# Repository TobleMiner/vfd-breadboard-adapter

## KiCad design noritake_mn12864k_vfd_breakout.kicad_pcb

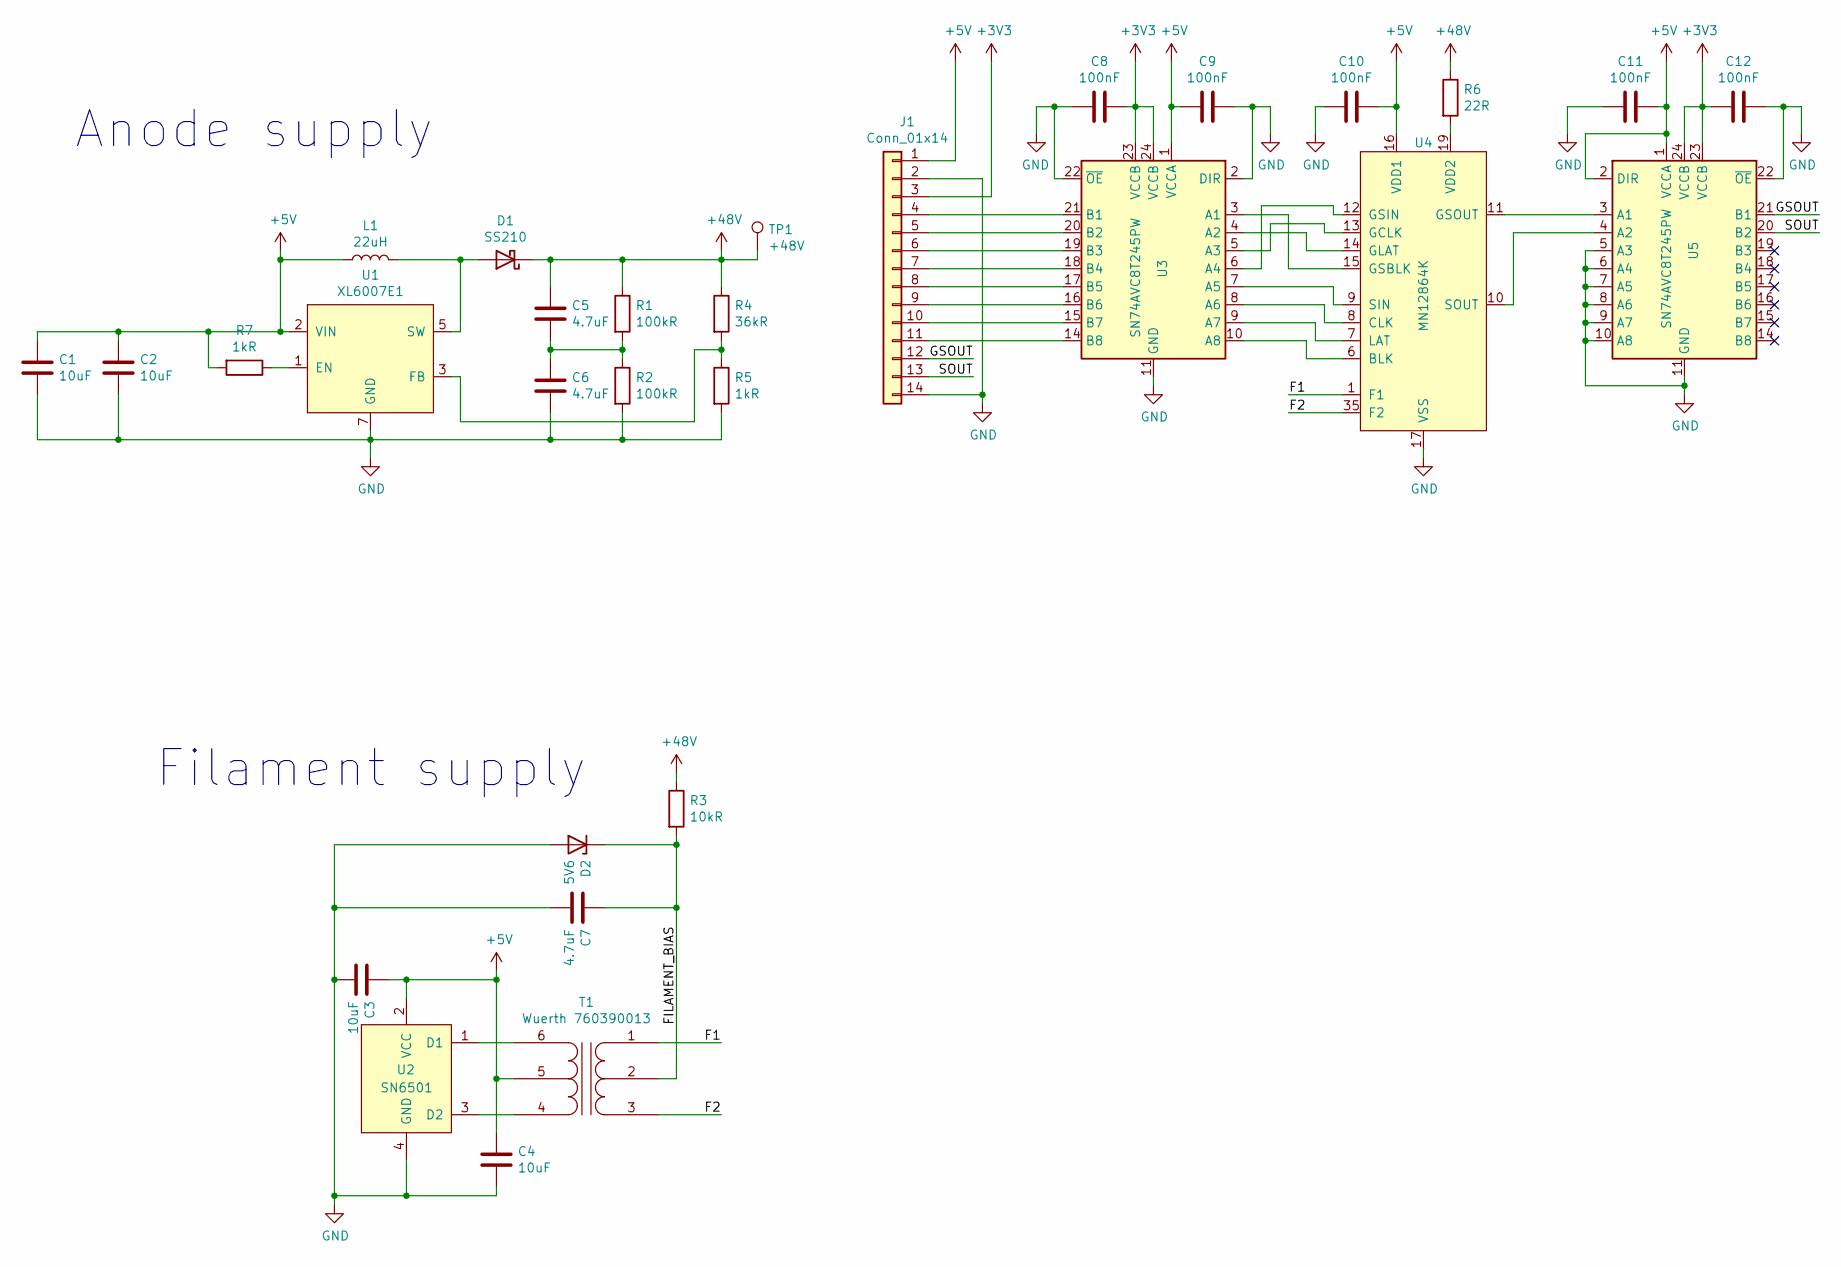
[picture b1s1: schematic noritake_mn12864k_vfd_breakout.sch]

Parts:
C1, C2, C3: 10uF; C_0805_2012Metric; LCSC C15850
C4: 10uF; C_1206_3216Metric; LCSC C13585
C5, C6, C7: 4.7uF; C_1206_3216Metric; LCSC C29823
C8, C9, C10, C11, C12: 100nF; C_0402_1005Metric; LCSC C1525
D1: SS210; D_SMA; LCSC C14996
D2: 5V6; D_MiniMELF; LCSC C8062
J1: Conn_01x14; PinHeader_1x14_P2.54mm_Vertical
L1: 22uH; MWSA0503S; LCSC C408340
R1, R2: 100kR; R_0805_2012Metric; LCSC C17407
R3: 10kR; R_1206_3216Metric; LCSC C17902
R4: 36kR; R_0805_2012Metric; LCSC C4360
R5, R7: 1kR; R_0402_1005Metric; LCSC C25905
R6: 22R; R_1206_3216Metric; LCSC C17958
T1: Wuerth 760390013; Transformer_Würth_10.05x6.73_6P
TP1: +48V; TestPoint_Pad_2.0x2.0mm
U1: XL6007E1; SO-8_3.9x4.9mm_P1.27mm; LCSC C73334
U2: SN6501; SOT-23-5
U3, U5: SN74AVC8T245PW; TSSOP-24_4.4x7.8mm_P0.65mm
U4: MN12864K

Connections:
+3V3: C8.1, C12.1, J1.3, U3.23 (VCCB), U3.24 (VCCB), U5.23 (VCCB), U5.24 (VCCB)
+5V: C1.1, C2.1, C3.1, C4.2, C9.2, C10.1, C11.2, J1.1, L1.1, R7.2, T1.5, U1.2 (VIN), U2.2 (VCC), U3.1 (VCCA), U4.16 (VDD1), U5.1 (VCCA), U5.2 (DIR)
+48V: C5.1, D1.1 (K), R1.1, R3.1, R4.1, R6.1, TP1.1
/F1: T1.1, U4.1 (F1), U4.2 (F1), U4.3 (F1)
/F2: T1.3, U4.35 (F2), U4.36 (F1), U4.37 (F1)
/FILAMENT_BIAS: C7.1, D2.1 (K), R3.2, T1.2
/GSOUT: J1.12, U5.21 (B1)
/SOUT: J1.13, U5.20 (B2)
GND: C1.2, C2.2, C3.2, C4.1, C6.2, C7.2, C8.2, C9.1, C10.2, C11.1, C12.2, D2.2 (A), J1.2, J1.14, R2.2, R5.2, U1.7 (GND), U1.8 (GND), U2.4 (GND), U2.5 (GND), U3.2 (DIR), U3.11 (GND), U3.12 (GND), U3.13 (GND), U3.22 (~OE), U4.17 (VSS), U4.18 (VSS), U5.5 (A3), U5.6 (A4), U5.7 (A5), U5.8 (A6), U5.9 (A7), U5.10 (A8), U5.11 (GND), U5.12 (GND), U5.13 (GND), U5.22 (~OE)
unnamed: C5.2, C6.1, R1.2, R2.1
unnamed: D1.2 (A), L1.2, U1.5 (SW), U1.6 (SW)
unnamed: J1.4, U3.21 (B1)
unnamed: J1.5, U3.20 (B2)
unnamed: J1.6, U3.19 (B3)
unnamed: J1.7, U3.18 (B4)
unnamed: J1.8, U3.17 (B5)
unnamed: J1.9, U3.16 (B6)
unnamed: J1.10, U3.15 (B7)
unnamed: J1.11, U3.14 (B8)
unnamed: R4.2, R5.1, U1.3 (FB)
unnamed: R7.1, U1.1 (EN)
unnamed: T1.4, U2.3 (D2)
unnamed: T1.6, U2.1 (D1)
unnamed: U3.3 (A1), U4.15 (GSBLK)
unnamed: U3.4 (A2), U4.14 (GLAT)
unnamed: U3.5 (A3), U4.13 (GCLK)
unnamed: U3.6 (A4), U4.12 (GSIN)
unnamed: U3.7 (A5), U4.9 (SIN)
unnamed: U3.8 (A6), U4.8 (CLK)
unnamed: U3.9 (A7), U4.7 (LAT)
unnamed: U3.10 (A8), U4.6 (BLK)
unnamed: U4.10 (SOUT), U5.4 (A2)
unnamed: U4.11 (GSOUT), U5.3 (A1)
VDD2: R6.2, U4.19 (VDD2), U4.20 (VDD2)

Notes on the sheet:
Filament supply
Anode supply

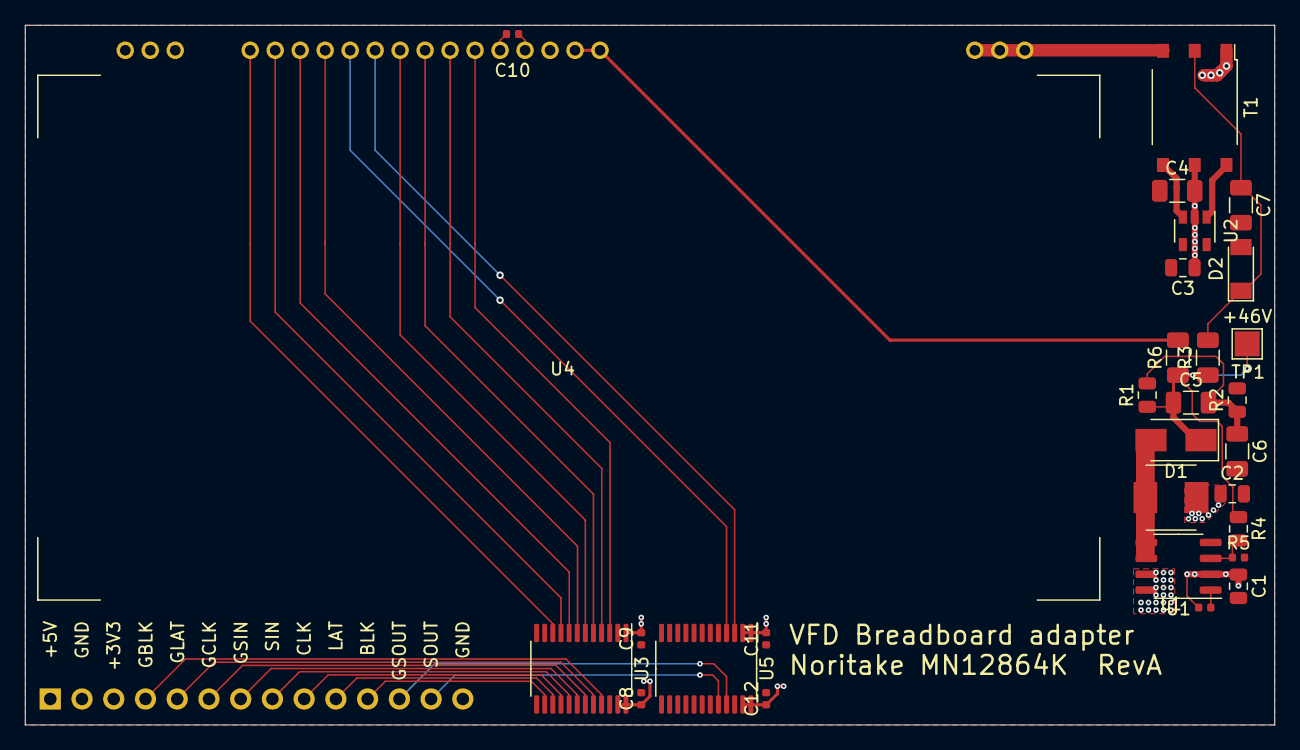
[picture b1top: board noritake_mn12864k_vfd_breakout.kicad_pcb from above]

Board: 4 copper layers, 100.0 x 56.0 mm, 30 parts (1 on the bottom side), 34 nets.

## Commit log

2020-09-10 Finish layout for assembly
2020-09-30 Fix 1kR LCSC partnumber
